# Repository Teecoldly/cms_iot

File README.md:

@teecoldly   <br>
Libaryname version <br>
DHT 1.3.6   https://github.com/adafruit/DHT-sensor-library <br>
sps30 1.3.7 https://github.com/paulvha/sps30 <br>
Air_Quality_Sensor 1.0.1 https://github.com/Seeed-Studio/Grove_Air_quality_Sensor <br>
MAX44009 1.0.0 https://github.com/dantudose/MAX44009 <br>
SocketIoClient 0.3 https://github.com/timum-viw/socket.io-client

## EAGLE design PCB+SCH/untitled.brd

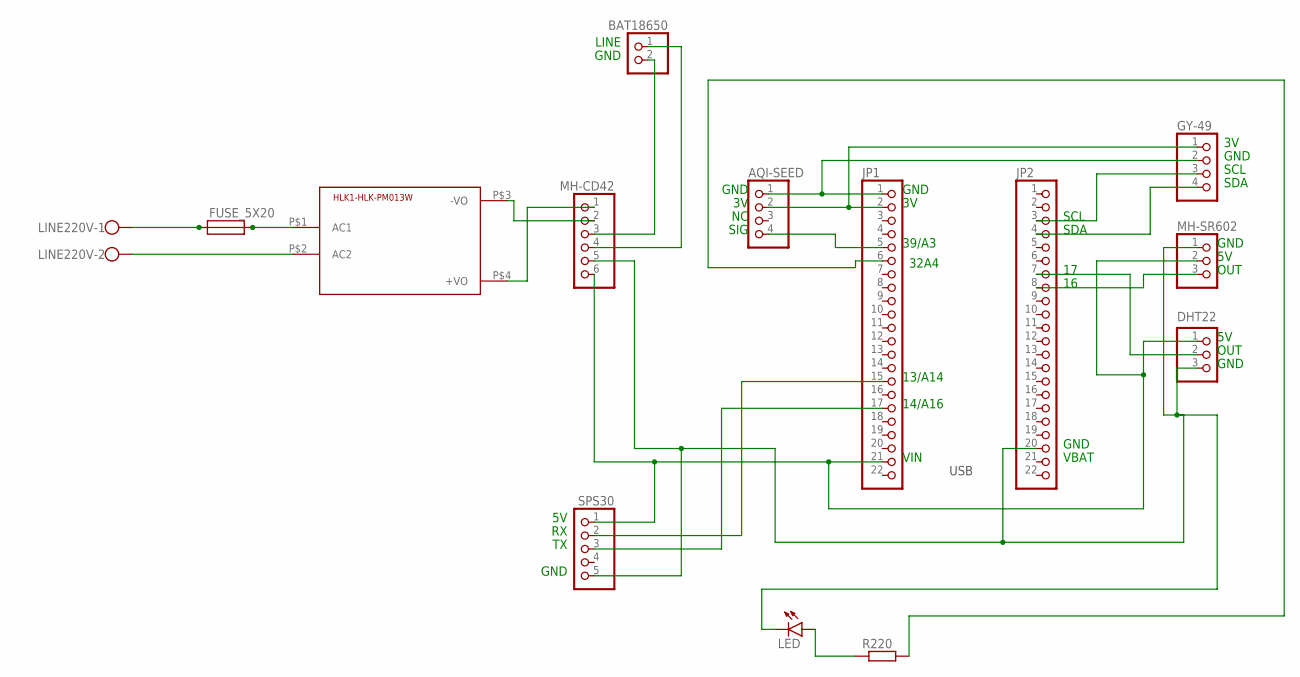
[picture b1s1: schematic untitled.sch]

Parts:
AQI-SEED: PINHD-1X4; 1X04
BAT18650: PINHD-1X2; 1X02
FUSE_5X20: FH_5X20
GY-49: PINHD-1X4; 1X04
HLK1-HLK-PM013W: HLK-PM013W; HLK-PM01
JP1, JP2: PINHD-1X22; 1X22
JP6: DHT22; 1X03
LED: LED3MM
LINE220V: W237-102
MH-CD42: PINHD-1X6; 1X06
MH-SR602: PINHD-1X3; 1X03
R220: R-EU_0204/5; 0204/5
SPS30: PINHD-1X5; 1X05

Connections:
unnamed: FUSE_5X20.1A, FUSE_5X20.1B, LINE220V.1
unnamed: FUSE_5X20.2A, FUSE_5X20.2B, HLK1-HLK-PM013W.P$1 (AC1)
unnamed: HLK1-HLK-PM013W.P$2 (AC2), LINE220V.2
unnamed: HLK1-HLK-PM013W.P$4 (+VO), MH-CD42.1
unnamed: HLK1-HLK-PM013W.P$3 (-VO), MH-CD42.2
unnamed: JP1.21, JP6.1, MH-CD42.6, MH-SR602.2, SPS30.1
unnamed: JP2.20, JP6.3, LED.K (C), MH-CD42.5, MH-SR602.1, SPS30.5
unnamed: JP2.7, JP6.2
unnamed: JP2.8, MH-SR602.3
unnamed: GY-49.4, JP2.4
unnamed: GY-49.3, JP2.3
unnamed: AQI-SEED.2, GY-49.1, JP1.2
unnamed: AQI-SEED.1, GY-49.2, JP1.1
unnamed: AQI-SEED.4, JP1.5
unnamed: JP1.15, SPS30.2
unnamed: LED.A, R220.1
unnamed: JP1.17, SPS30.3
unnamed: BAT18650.2, MH-CD42.3
unnamed: BAT18650.1, MH-CD42.4
unnamed: JP1.6, R220.2

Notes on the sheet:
GND
39/A3
VIN
USB
OUT
SCL
SDA
SIG
VBAT
14/A16
13/A14
LINE
32A4

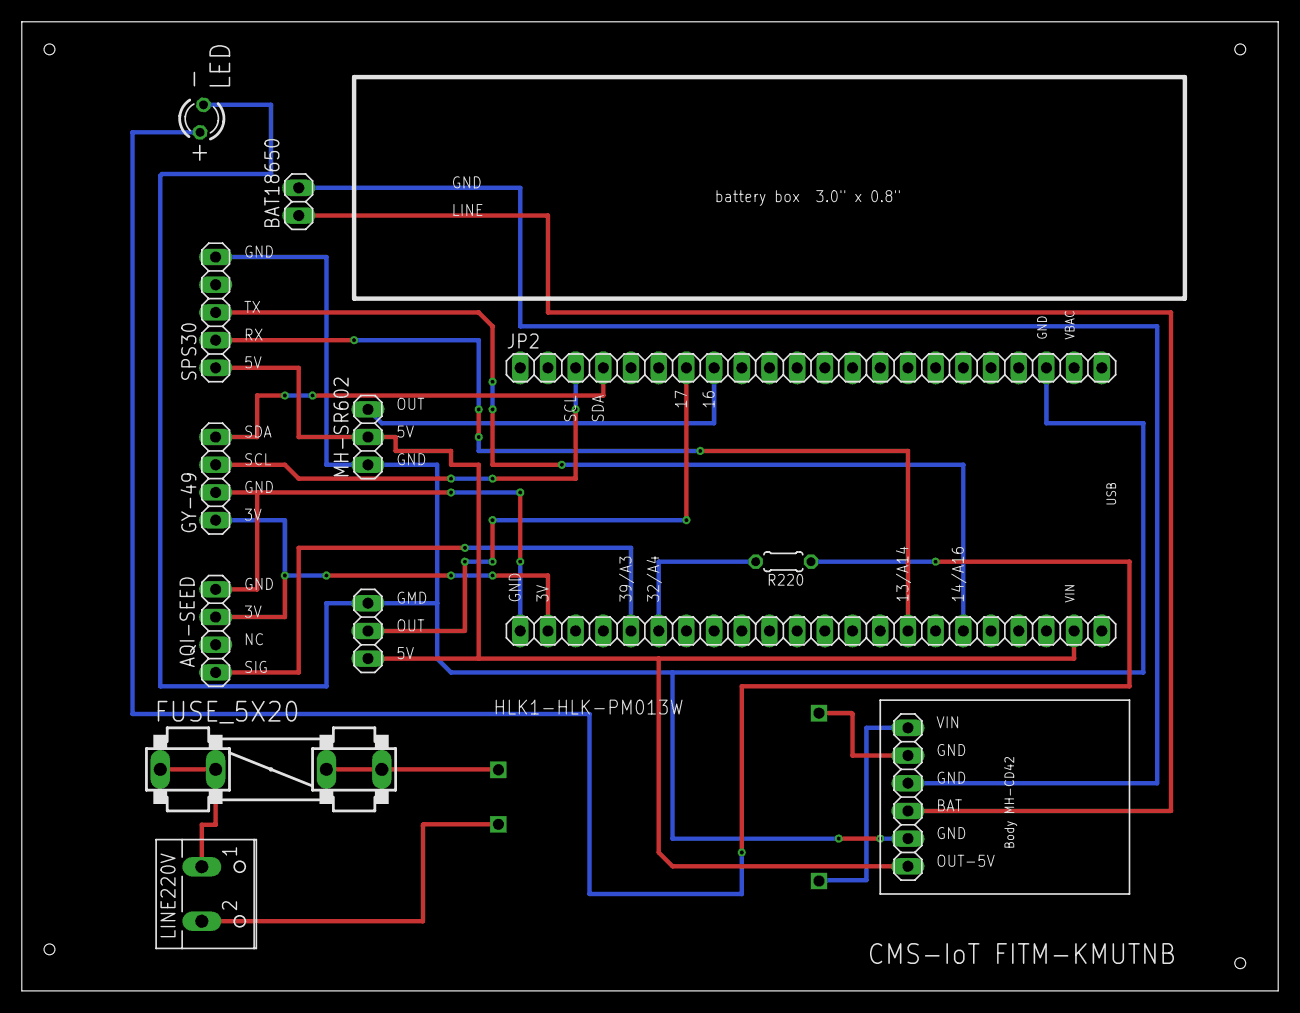
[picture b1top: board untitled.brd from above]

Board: 2 copper layers, 115.2 x 88.9 mm, 14 parts (0 on the bottom side), 20 nets.
